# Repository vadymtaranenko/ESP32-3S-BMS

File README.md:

#ESP32 3S BMS & Telemetry Node

Prosty, niezawodny system zarządzania pakietami Li-Po 3S oparty na mikrokontrolerze ESP32. Układ komunikuje się po magistrali SPI.

* **UVP / OVP (Under/Over-Voltage Protection):** Indywidualne monitorowanie napięcia każdej celi (domyślnie: min. 3.00 V, max. 4.20 V).
* **OCP (Over-Current Protection):** Ciągły pomiar poboru prądu pod obciążeniem (limit: 12.00 A).
* **OTP (Over-Temperature Protection):** Monitorowanie temperatury ogniw zapobiegające Thermal Runaway (limit: 50.0 °C).
* **Telemetria JSON:** Asynchroniczne wysyłanie ramek danych.

Specyfikacja Sprzętowa 

* **MCU:** ESP32-WROOM-32E (Moduł z Wi-Fi & Bluetooth, taktowanie do 240 MHz).
* **Zasilanie (Power Management):** Zintegrowana przetwornica Buck LM2596T-5 (obniżająca napięcie pakietu do 5V) oraz stabilizator LDO LD1086DT33TR (3.3V dla logiki). Wejście chronione przed odwrotną polaryzacją za pomocą P-MOSFETa.
* **Interfejs USB & Flash:** Złącze USB-C z zabezpieczeniem ESD (USBLC6-2SC6). Wbudowany konwerter USB-UART na układzie CH340C z obwodem Auto-Reset umożliwiającym płynne programowanie.
* **Pomiar Napięcia:** Indywidualny odczyt napięć na celach (V1+, V2+, V3+). Dzielniki rezystorowe załączane dynamicznie przez N-MOSFETy i separowane optoizolatorami (SFH617A), co całkowicie eliminuje problem samorozładowania pakietu.
* **Pomiar Prądu:** Pomiar na dedykowanym wzmacniaczu operacyjnym INA213 współpracującym z rezystorem bocznikowym (Shunt) 10 mΩ.
* **Pomiar Temperatury:** Dwutorowy układ pomiarowy: klasyczny termistor NTC oraz analogowy tor dla czujnika PT100 zrealizowany na układzie LM324.
* **Load Switch:** Sprzętowe odłączanie obciążenia (High-Side) realizowane za pomocą tranzystorów P-MOSFET IRF4905 sterowanych złączami optoizolowanymi.

##Struktura Repozytorium
* **`README.md`** - Główna dokumentacja projektu.
* **`/.gitignore`** - Reguły ignorowania plików tymczasowych (m m.in. KiCada i środowisk programistycznych).
* **`/Hardware`** - Pliki źródłowe projektu (schematy i projekt PCB) wykonane w programie KiCad.
* **`/Firmware`** - Kod źródłowy dla mikrokontrolera ESP32.
* **`/Docs`** - Dokumentacja dodatkowa (schematy w formacie PDF, rendery 3D).

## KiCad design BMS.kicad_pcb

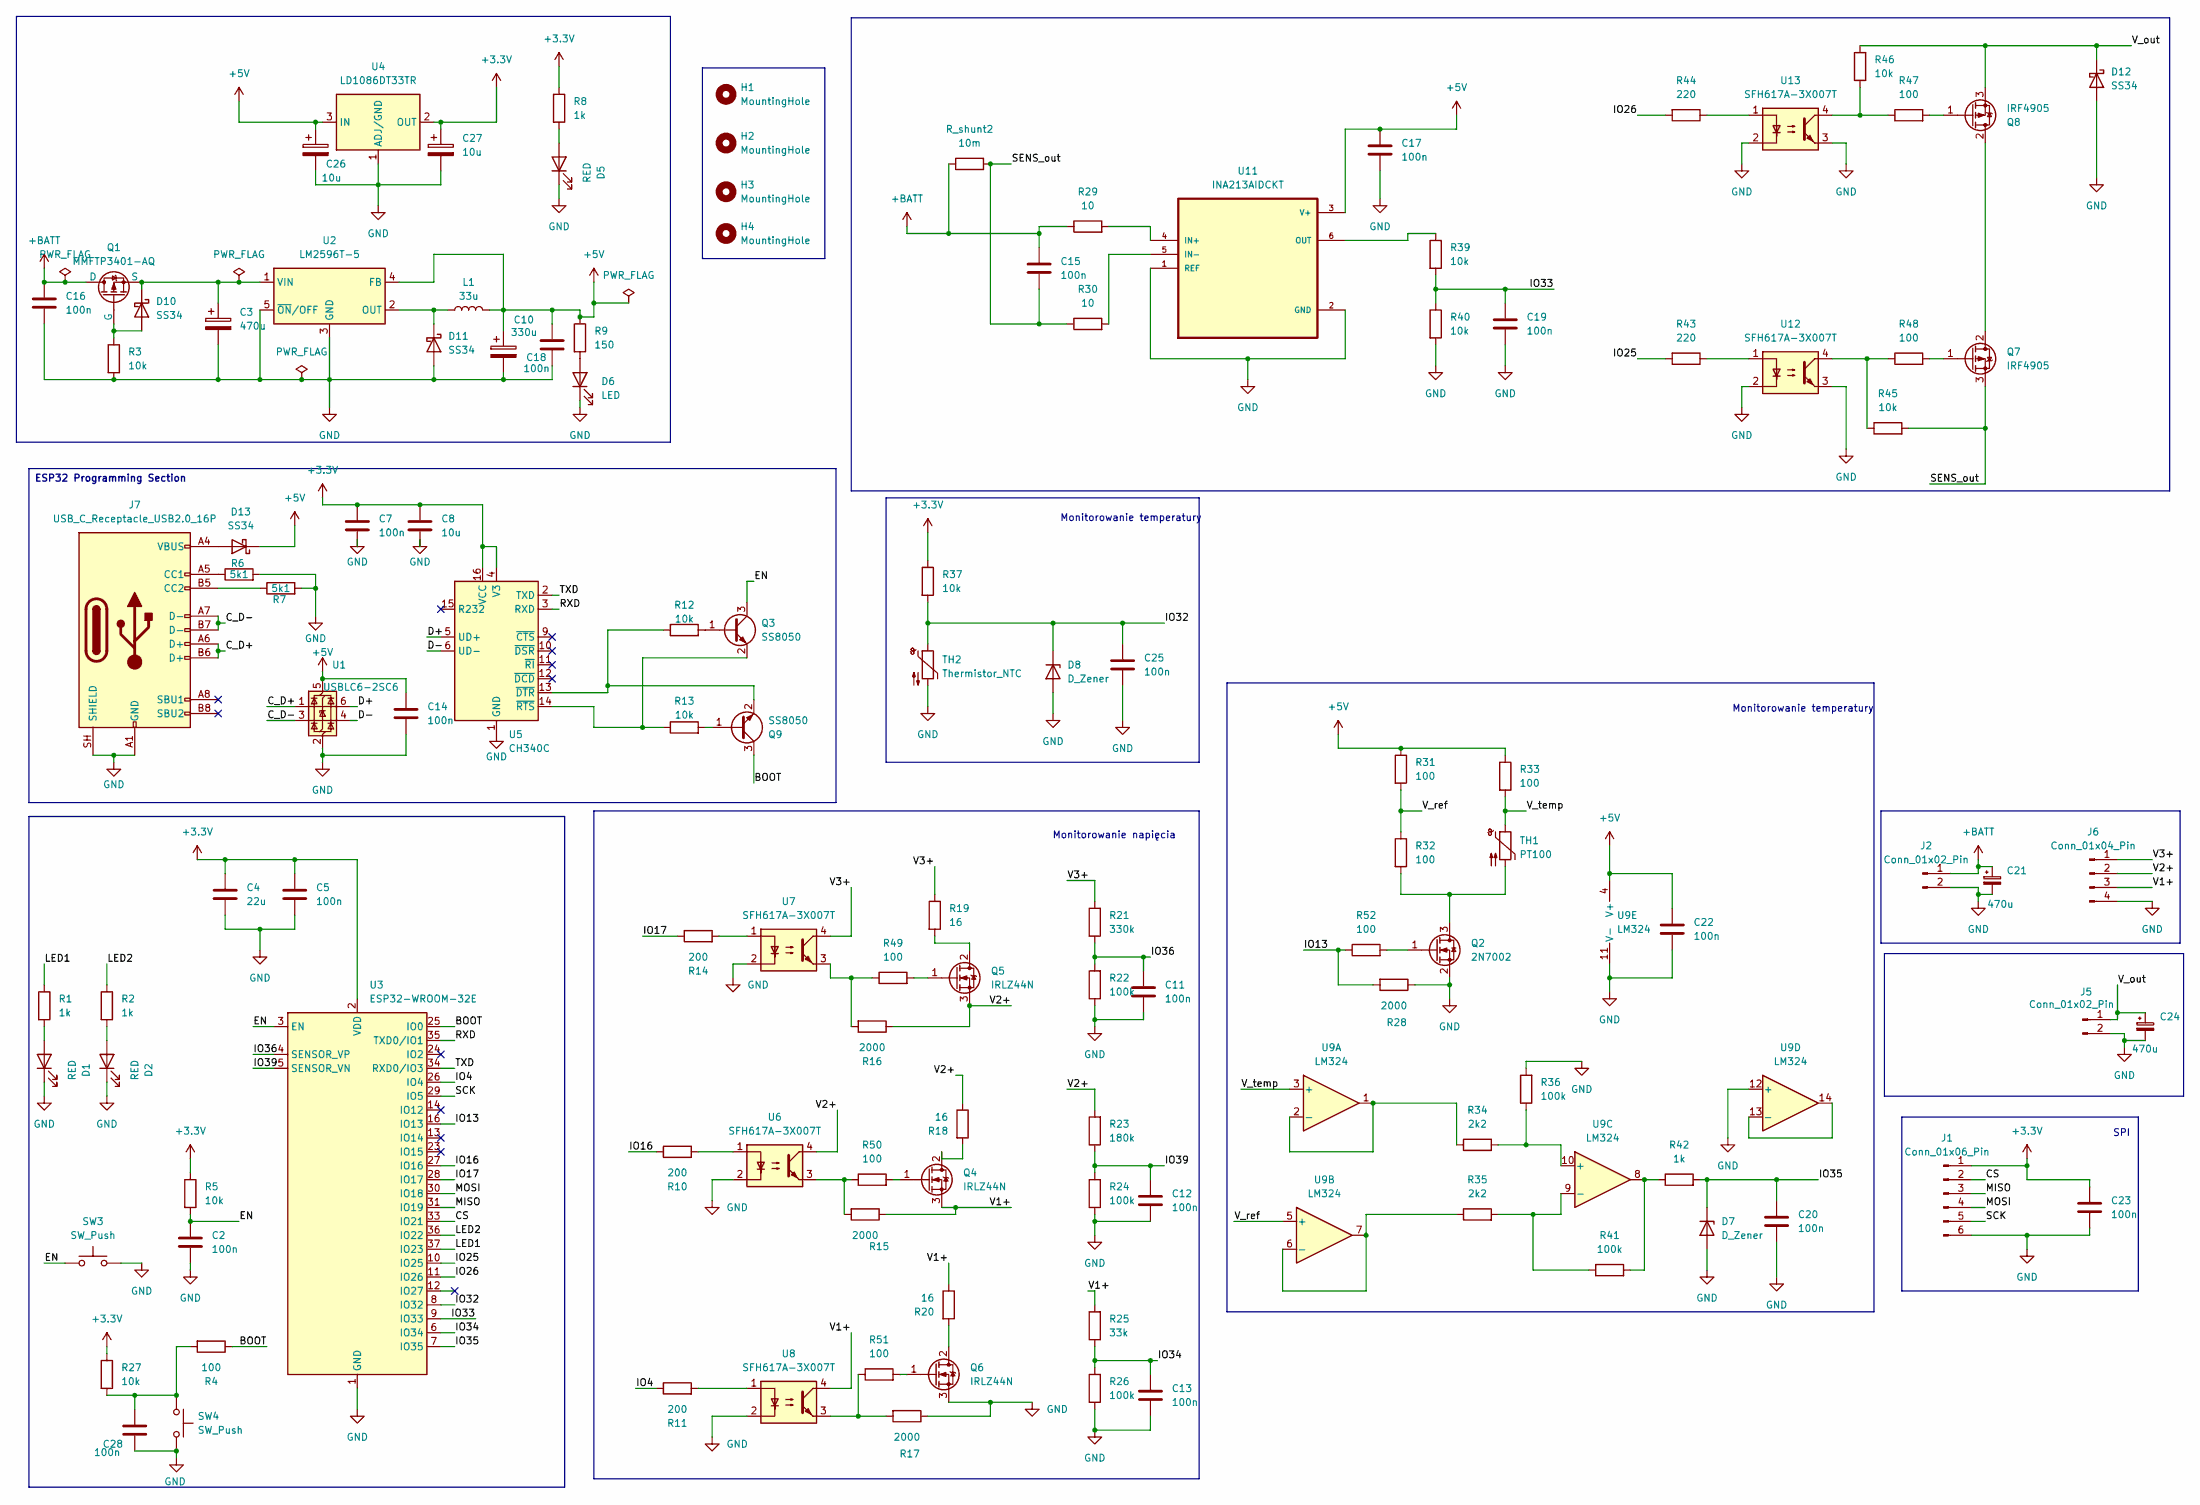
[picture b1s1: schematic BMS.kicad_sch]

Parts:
C2: 100n; CP_Elec_5x4.5
C3, C21, C24: 470u; CP_Elec_5x4.5
C4: 22u; CP_Elec_5x4.5
C5, C7, C11, C12, C13, C14, C15, C16, C17, C18, C19, C20, C22, C23, C25: 100n; C_0805_2012Metric_Pad1.18x1.45mm_HandSolder
C8: 10u; C_0805_2012Metric_Pad1.18x1.45mm_HandSolder
C10: 330u; CP_Elec_5x4.5
C26, C27: 10u; CP_Elec_5x4.5
C28: 100n; C_0603_1608Metric
D1, D2, D5: RED; LED_0805_2012Metric_Pad1.15x1.40mm_HandSolder
D6: LED; LED_0805_2012Metric_Pad1.15x1.40mm_HandSolder
D7, D8: D_Zener; D_SOD-323_HandSoldering
D10, D11, D12, D13: SS34; D_SMB_Handsoldering
H1, H2, H3, H4: MountingHole; MountingHole_2.2mm_M2_ISO7380
J1: Conn_01x06_Pin; PinHeader_1x06_P2.54mm_Vertical
J2, J5: Conn_01x02_Pin; AMASS_XT60-F_1x02_P7.20mm_Vertical
J6: Conn_01x04_Pin; JST_EH_B4B-EH-A_1x04_P2.50mm_Vertical
J7: USB_C_Receptacle_USB2.0_16P; USB_C_Receptacle_GCT_USB4105-xx-A_16P_TopMnt_Horizontal
L1: 33u; L_Panasonic_PCC-M0630M
Q1: MMFTP3401-AQ; SOT-23-3
Q2: 2N7002; SOT-23_Handsoldering
Q3, Q9: SS8050; SOT-23
Q4, Q5, Q6: IRLZ44N; TO-220-3_Vertical
Q7, Q8: IRF4905; TO-220-3_Vertical
R1, R2, R8, R42: 1k; R_0805_2012Metric_Pad1.20x1.40mm_HandSolder
R3, R5, R12, R13, R27, R37, R39, R40, R45, R46: 10k; R_0805_2012Metric_Pad1.20x1.40mm_HandSolder
R4, R31, R32, R33, R47, R48, R49, R50, R51, R52: 100; R_0805_2012Metric_Pad1.20x1.40mm_HandSolder
R6, R7: 5k1; R_0805_2012Metric_Pad1.20x1.40mm_HandSolder
R9: 150; R_0805_2012Metric_Pad1.20x1.40mm_HandSolder
R10, R11, R14: 200; R_0805_2012Metric_Pad1.20x1.40mm_HandSolder
R15, R16, R17, R28: 2000; R_0805_2012Metric_Pad1.20x1.40mm_HandSolder
R18, R19, R20: 16; R_Axial_DIN0614_L14.3mm_D5.7mm_P5.08mm_Vertical
R21: 330k; R_0805_2012Metric_Pad1.20x1.40mm_HandSolder
R22, R24, R26, R36, R41: 100k; R_0805_2012Metric_Pad1.20x1.40mm_HandSolder
R23: 180k; R_0805_2012Metric_Pad1.20x1.40mm_HandSolder
R25: 33k; R_0805_2012Metric_Pad1.20x1.40mm_HandSolder
R29, R30: 10; R_0805_2012Metric_Pad1.20x1.40mm_HandSolder
R34, R35: 2k2; R_0805_2012Metric_Pad1.20x1.40mm_HandSolder
R43, R44: 220; R_0805_2012Metric_Pad1.20x1.40mm_HandSolder
R_shunt2: 10m; R_2512_6332Metric_Pad1.40x3.35mm_HandSolder
SW3, SW4: SW_Push; SW_PUSH_6mm_H9.5mm
TH1: PT100; PinHeader_1x02_P2.54mm_Vertical
TH2: Thermistor_NTC; PinHeader_1x02_P2.54mm_Vertical
U1: USBLC6-2SC6; SOT-23-6
U2: LM2596T-5; TO-220-5_P3.4x3.7mm_StaggerOdd_Lead3.8mm_Vertical
U3: ESP32-WROOM-32E; ESP32-WROOM-32D
U4: LD1086DT33TR; TO-263-3_TabPin2
U5: CH340C; SOIC-16_3.9x9.9mm_P1.27mm
U6, U7, U8, U12, U13: SFH617A-3X007T; SMDIP-4_W9.53mm_Clearance8mm
U9: LM324; SOIC-14_3.9x8.7mm_P1.27mm
U11: INA213AIDCKT; SOT-363_SC-70-6_Handsoldering

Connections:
+3.3V: C4.1, C5.1, C7.1, C8.1, C23.1, C27.1, J1.1, R5.1, R8.1, R27.1, R37.1, U3.2 (VDD), U4.2 (OUT), U5.4 (V3), U5.16 (VCC)
+5V: C10.1, C14.1, C17.1, C18.1, C22.1, C26.1, D13.1 (K), L1.2, R9.1, R31.1, R33.1, U1.5 (VBUS), U2.4 (FB), U4.3 (IN), U9.4 (V+), U11.3 (V+)
+BATT: C15.1, C16.1, C21.1, J2.1, Q1.1 (D), R29.1, R_shunt2.1
/BOOT: Q9.3 (C), R4.1, U3.25 (IO0)
/CS: J1.2, U3.33 (IO21)
/C_D+: J7.A6 (D+), J7.B6 (D+), U1.1 (I/O1)
/C_D-: J7.A7 (D-), J7.B7 (D-), U1.3 (I/O2)
/D+: U1.6 (I/O1), U5.5 (UD+)
/D-: U1.4 (I/O2), U5.6 (UD-)
/EN: C2.1, Q3.3 (C), R5.2, SW3.1, U3.3 (EN)
/IO4: R11.1, U3.26 (IO4)
/IO13: R28.2, R52.1, U3.16 (IO13)
/IO16: R10.1, U3.27 (IO16)
/IO17: R14.1, U3.28 (IO17)
/IO25: R43.2, U3.10 (IO25)
/IO26: R44.2, U3.11 (IO26)
/IO32: C25.1, D8.1 (K), R37.2, TH2.1, U3.8 (IO32)
/IO33: C19.1, R39.2, R40.1, U3.9 (IO33)
/IO34: C13.1, R25.1, R26.2, U3.6 (IO34)
/IO35: C20.1, D7.1 (K), R42.2, U3.7 (IO35)
/IO36: C11.1, R21.1, R22.2, U3.4 (SENSOR_VP)
/IO39: C12.1, R23.1, R24.2, U3.5 (SENSOR_VN)
/LED1: R1.1, U3.37 (IO23)
/LED2: R2.1, U3.36 (IO22)
/MISO: J1.3, U3.31 (IO19)
/MOSI: J1.4, U3.30 (IO18)
/RXD: U3.35 (TXD0/IO1), U5.3 (RXD)
/SCK: J1.5, U3.29 (IO5)
/SENS_out: C15.2, Q7.3 (S), R30.1, R45.2, R_shunt2.2
/TXD: U3.34 (RXD0/IO3), U5.2 (TXD)
/V1+: J6.3, Q4.3 (S), R15.1, R20.1, R25.2, U8.4
/V2+: J6.2, Q5.3 (S), R16.1, R18.1, R23.2, U6.4
/V3+: J6.1, R19.1, R21.2, U7.4
/V_out: C24.1, D12.1 (K), J5.1, Q8.3 (S), R46.2
/V_ref: R31.2, R32.1, U9.5 (+)
/V_temp: R33.2, TH1.1, U9.3 (+)
GND: C2.2, C3.2, C4.2, C5.2, C7.2, C8.2, C10.2, C11.2, C12.2, C13.2, C14.2, C16.2, C17.2, C18.2, C19.2, C20.2, C21.2, C22.2, C23.2, C24.2, C25.2, C26.2, C27.2, C28.2, D1.1 (K), D2.1 (K), D5.1 (K), D6.1 (K), D7.2 (A), D8.2 (A), D11.2 (A), D12.2 (A), J1.6, J2.2, J5.2, J6.4, J7.A1 (GND), J7.A12 (GND), J7.B1 (GND), J7.B12 (GND), J7.SH (SHIELD), Q2.2 (S), Q6.3 (S), R3.2, R6.2, R7.2, R17.1, R22.1, R24.1, R26.1, R28.1, R36.2, R40.2, SW3.2, SW4.2, TH2.2, U1.2 (GND), U2.3 (GND), U2.5 (~ON/OFF), U3.1 (GND), U3.15 (GND), U3.38 (GND), U3.39 (GND), U4.1 (ADJ/GND), U5.1 (GND), U6.2, U7.2, U8.2, U9.11 (V-), U9.12 (+), U11.1 (REF), U11.2 (GND), U12.2, U12.3, U13.2, U13.3
unnamed: C28.1, R4.2, R27.2, SW4.1
unnamed: D1.2 (A), R1.2
unnamed: D2.2 (A), R2.2
unnamed: D5.2 (A), R8.2
unnamed: D6.2 (A), R9.2
unnamed: D10.2 (A), Q1.2 (G), R3.1
unnamed: C3.1, D10.1 (K), Q1.3 (S), U2.1 (VIN)
unnamed: D11.1 (K), L1.1, U2.2 (OUT)
unnamed: D13.2 (A), J7.A4 (VBUS), J7.A9 (VBUS), J7.B4 (VBUS), J7.B9 (VBUS)
unnamed: J7.A5 (CC1), R6.1
unnamed: J7.B5 (CC2), R7.1
unnamed: Q2.3 (D), R32.2, TH1.2
unnamed: Q2.1 (G), R52.2
unnamed: Q3.1 (B), R12.2
unnamed: Q3.2 (E), R13.1, U5.14 (~RTS)
unnamed: Q4.2 (D), R18.2
unnamed: Q4.1 (G), R50.2
unnamed: Q5.2 (D), R19.2
unnamed: Q5.1 (G), R49.2
unnamed: Q6.2 (D), R20.2
unnamed: Q6.1 (G), R51.2
unnamed: Q7.2 (D), Q8.2 (D)
unnamed: Q7.1 (G), R48.2
unnamed: Q8.1 (G), R47.2
unnamed: Q9.1 (B), R13.2
unnamed: Q9.2 (E), R12.1, U5.13 (~DTR)
unnamed: R10.2, U6.1
unnamed: R11.2, U8.1
unnamed: R14.2, U7.1
unnamed: R15.2, R50.1, U6.3
unnamed: R16.2, R49.1, U7.3
unnamed: R17.2, R51.1, U8.3
unnamed: R41.2, R42.1, U9.8
unnamed: R43.1, U12.1
unnamed: R44.1, U13.1
unnamed: R45.1, R48.1, U12.4
unnamed: R46.1, R47.1, U13.4
unnamed: R34.1, U9.1, U9.2 (-)
unnamed: R35.1, U9.6 (-), U9.7
unnamed: R34.2, R36.1, U9.10 (+)
unnamed: R35.2, R41.1, U9.9 (-)
unnamed: U9.13 (-), U9.14
unnamed: R29.2, U11.4 (IN+)
unnamed: R30.2, U11.5 (IN-)
unnamed: R39.1, U11.6 (OUT)

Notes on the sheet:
SPI
Monitorowanie temperatury
Monitorowanie napięcia
ESP32 Programming Section

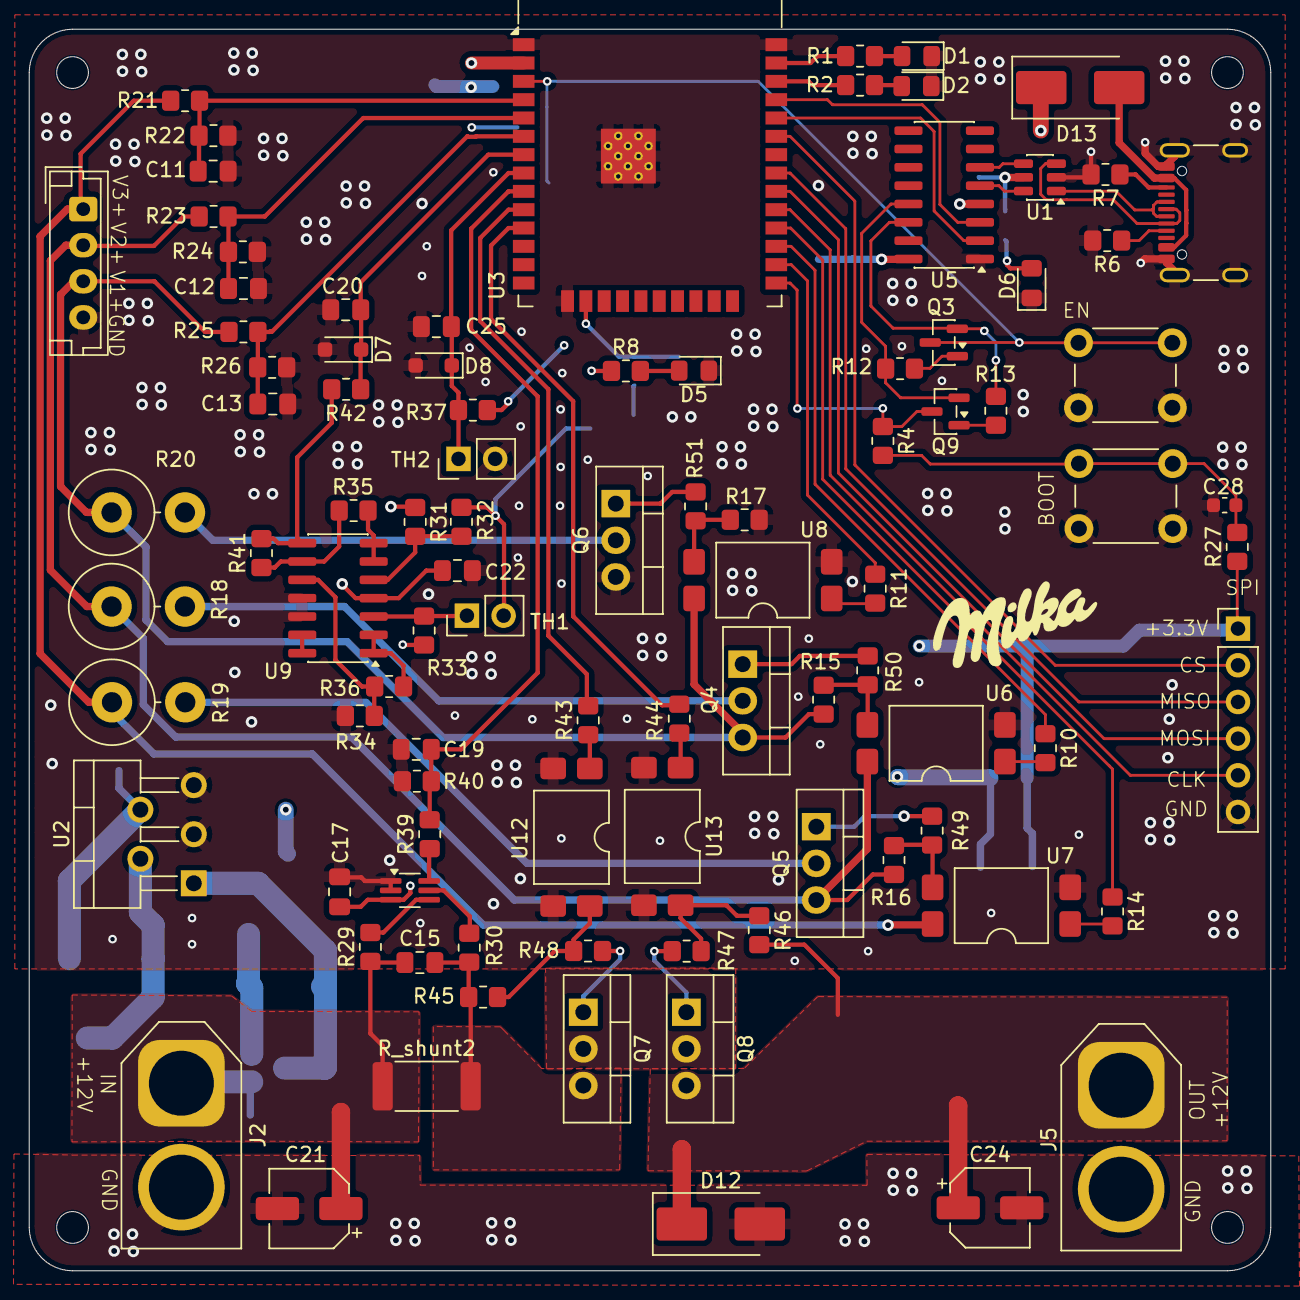
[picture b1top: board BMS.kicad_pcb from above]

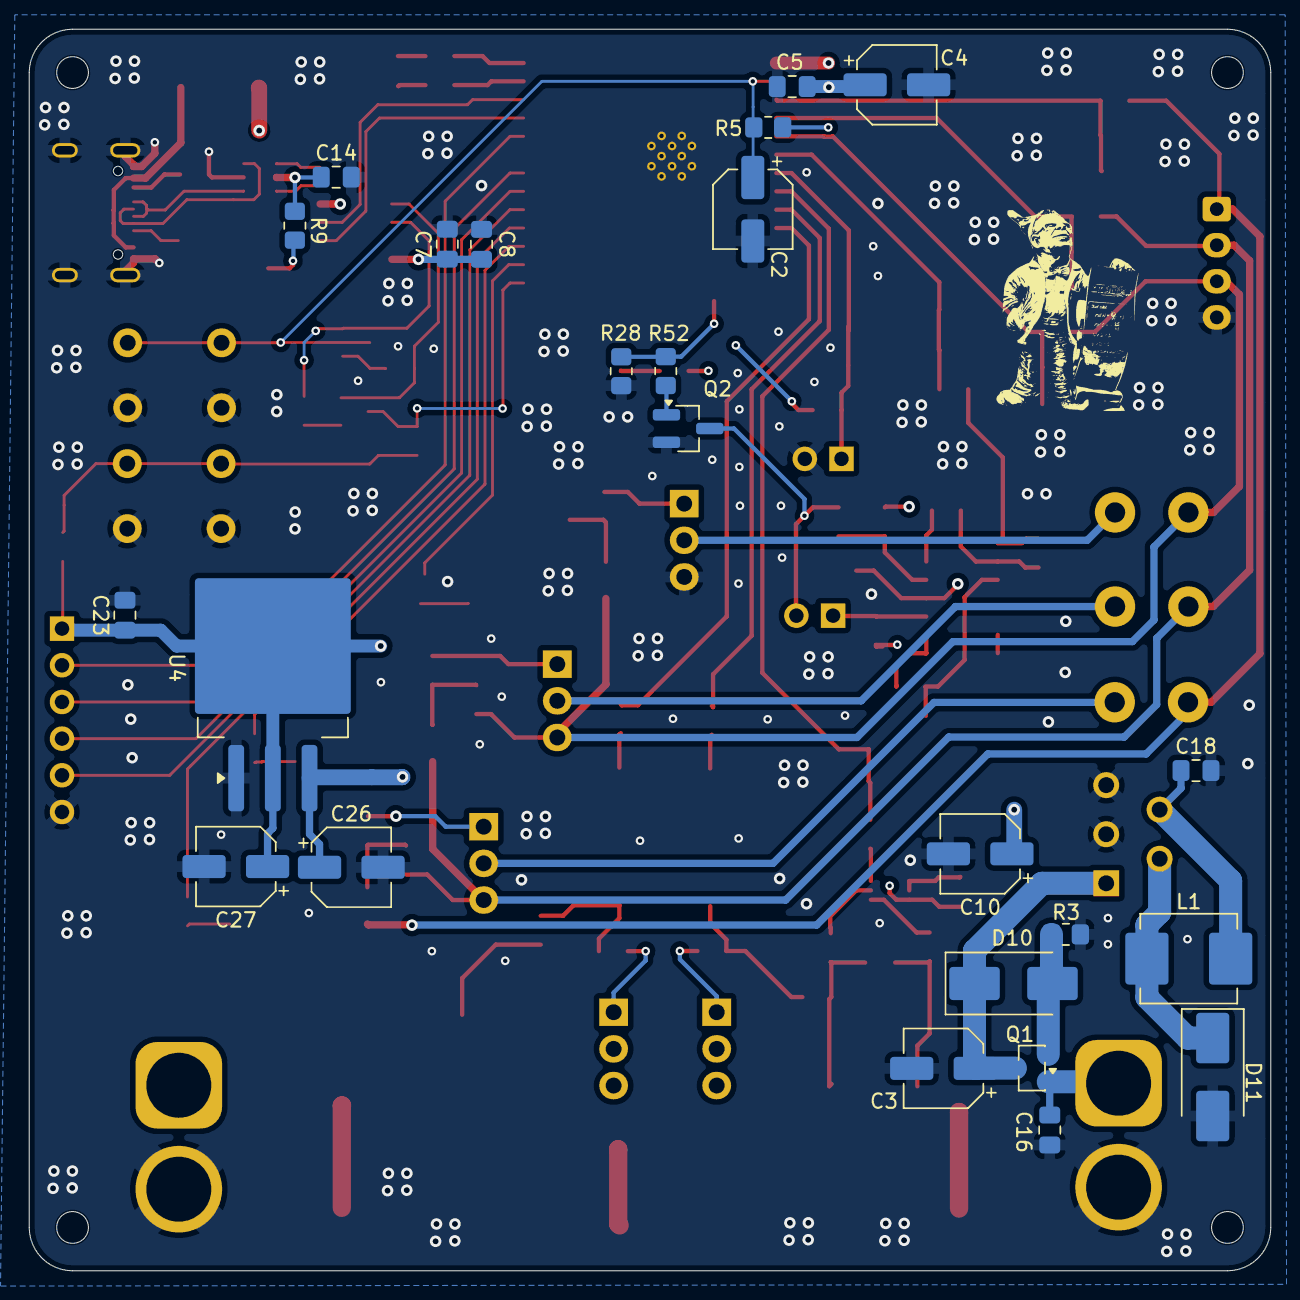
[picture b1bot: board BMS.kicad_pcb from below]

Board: 4 copper layers, 86.0 x 86.0 mm, 122 parts (24 on the bottom side), 82 nets.

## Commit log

2026-04-18 added foot_prints
2026-04-18 deklaracja warstw
2026-04-18 pierwszy krok
2026-04-20 linki do TME
2026-04-21 update0.2
2026-04-21 rezystory po 100 ohm do pt100
2026-04-21 update0.3
2026-04-21 Dodanie resystora do PT100
2026-04-21 update0.4
2026-04-21 clean up
2026-04-21 L1_47u
2026-04-25 poprawa
2026-04-27 przetwornica
2026-04-28 Dioda
2026-04-28 KOndensator
2026-04-28 rezystor V_out
2026-04-28 poprawiłem
2026-04-28 MILKA
